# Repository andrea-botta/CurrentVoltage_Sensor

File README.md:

# Current and Voltage Sensor
*KiCAD project for a Current and Voltage sensor PCB*

This sensor is based around the LTC4151 current and voltage monitor

By deafult a 1.5 mOhm shunt is used, providing a maximum measurable current of 54 A. The voltage range is 7-80 V.  

## Schematic
![[Link to PDF]](docs/schematics.pdf)

## Arduino code
[[Link to Library by Kerry D. Wong]](http://www.kerrywong.com/2014/04/19/arduino-library-for-ltc4151/)

The same link is also available [here](arduino/)

Note that the sensor I2C address can be changes using the solder jumper on the back to change the state of ADR0 and ADR1 to L (Low), H (High) or F (not connected)

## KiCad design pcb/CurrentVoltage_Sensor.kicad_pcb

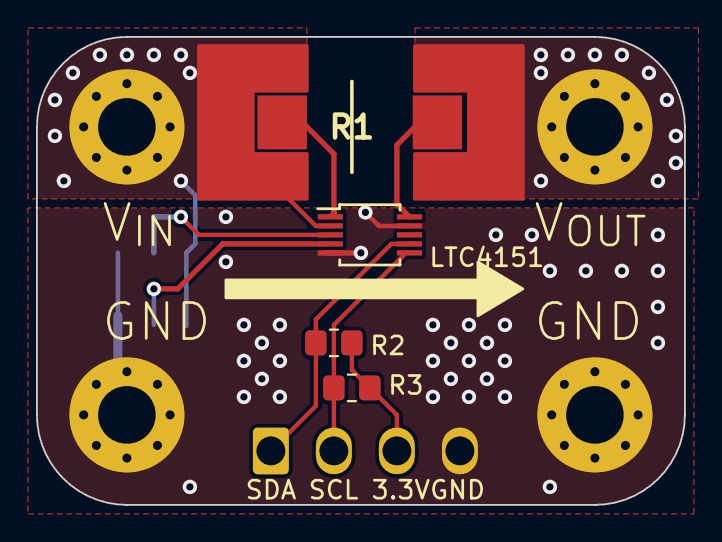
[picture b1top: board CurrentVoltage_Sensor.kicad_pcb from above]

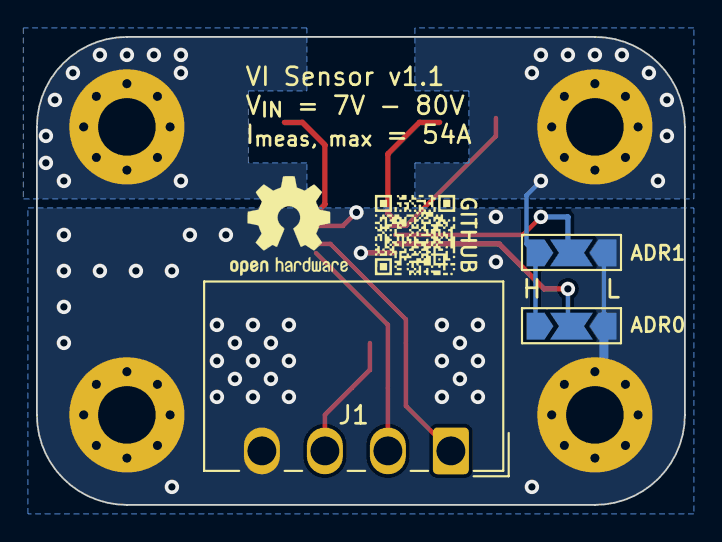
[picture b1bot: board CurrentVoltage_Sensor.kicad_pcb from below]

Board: 2 copper layers, 36.0 x 26.0 mm, 11 parts (3 on the bottom side), 10 nets.

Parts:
ADR0, ADR1: SolderJumper_3_Open; SolderJumper-3_P2.0mm_Open_TrianglePad1.0x1.5mm_NumberLabels
H1, H2, H5, H6: MountingHole_Pad; MountingHole_3.2mm_M3_Pad_Via
J1: Wago_734-164_1x04_P3.50mm; Wago_734-164_1x04_P3.50mm_Horizontal
LTC4151: LTC4151xMS; MSOP-10_3x3mm_P0.5mm
R1: HoLRS1575-1.5mR-1%; RESC10052X90N
R2, R3: 2k; R_0805_2012Metric_Pad1.20x1.40mm_HandSolder

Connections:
+3.3V: J1.3, R2.1, R3.1
+BATT: ADR0.1 (A), ADR1.1 (A), H1.1, LTC4151.2 (VIN), R1.1
/ADR0: ADR0.2 (C), LTC4151.4 (ADR0)
/ADR1: ADR1.2 (C), LTC4151.3 (ADR1)
/SCL: J1.2, LTC4151.6 (SCL), R3.2
/SDA: J1.1, LTC4151.7 (SDA), R2.2
/Sense_{+}: LTC4151.1 (SENSE+), R1.3 (SENSE+)
/Sense_{-}: LTC4151.10 (SENSE-), R1.4 (SENSE-)
/V_{out}: H2.1, R1.2
GND: ADR0.3 (B), ADR1.3 (B), H5.1, H6.1, J1.4, LTC4151.5 (ADIN), LTC4151.9 (GND)

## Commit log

2025-02-19 README update
2025-02-19 PCB update
2025-04-24 PCB v1.1 - Fixed some PCB traces
2025-04-24 Updated ReadME, added link to Arduino Library, added possible logos
